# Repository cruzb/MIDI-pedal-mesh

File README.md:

# MIDI Pedal and Mesh
Digital music production today has a lot of limits. In an analog world a musician can slightly tweak the angle of their bow on a violin to get a different sound. The aim of the “Mesh” is to create a digital instrument with analog levels of control in package compatible with existing digital workflows.

Effects pedals are a common tool used by guitarists to modify the sound of their instrument. These devices are often designed to make one specific sound. The aim of the “Pedal” is to create a customizable audio processing device that gives users direct access to DSP hardware while maintaining the functionality and ease of use that musicians expect.

### Watch this video to see it in action

## Implementation
### Overview
The Mesh and Pedal work as standard audio components that can fit seamlessly into any musician’s kit. The Mesh outputs a MIDI signal which can be use to generate sound through any MIDI-capable synthesizer. The Pedal takes in analog audio and performs effects processing on it before outputting it to an amplifier or speaker for play. These devices can work in tandem, independently, or with other music devices.

### Pedal
- Users create effects programs on desktop and upload to the device EEPROM via a desktop application and USB connection
- Once loaded to the pedal programs can be selected via a knob
- An LCD screen in the pedal displays the active program and up to three associated parameters for it
- Input analog audio is split into two independent signal paths and processed by the selected program on an FV-1 DSP chip
- The affected signal then runs through an analog equalizer and is blended with the clean signal before it is output.

### Mesh
- Use strain sensors to read force data on two axes via ADC
- Use ADC data to do basic 2D localization of which point in grid is most pressed and by how much
- Map that point to a pitch, pitch-bend, and velocity for MIDI
- Generate MIDI packets from these data
- Send MIDI via UART at 31250 baud

## PCB Design
Three PCBs were created for this project. One for the pedal and two for the mesh. The pedal PCB contains over 160 components that handle digital and analog signals. The mesh PCBs are simpler but took special design considerations into account. Because of the analog nature of the device all analog runs were made as short as possible and processing occurs close to the sensors to deal with noise issues.

## Major Compontents
### Pedal
- PIC16F15355 Microcontroller
- FV-1 Spin Semiconductor DSP Chip
- HD44780-Compatible RGB 16x2 Character LCD
- FT232 USB-UART Interface
- 24LC32A External EEPROM Chip
- MAX4910ETE Audio Switch

### Mesh
- PIC16F15376 Microcontroller
- TAL221 Load Cell
- AD620 Differential Amplifier

#### Made with Jordan Frank, Ethan Brown, Charlie Light, and Spencer Haney for University of Michigan EECS 473

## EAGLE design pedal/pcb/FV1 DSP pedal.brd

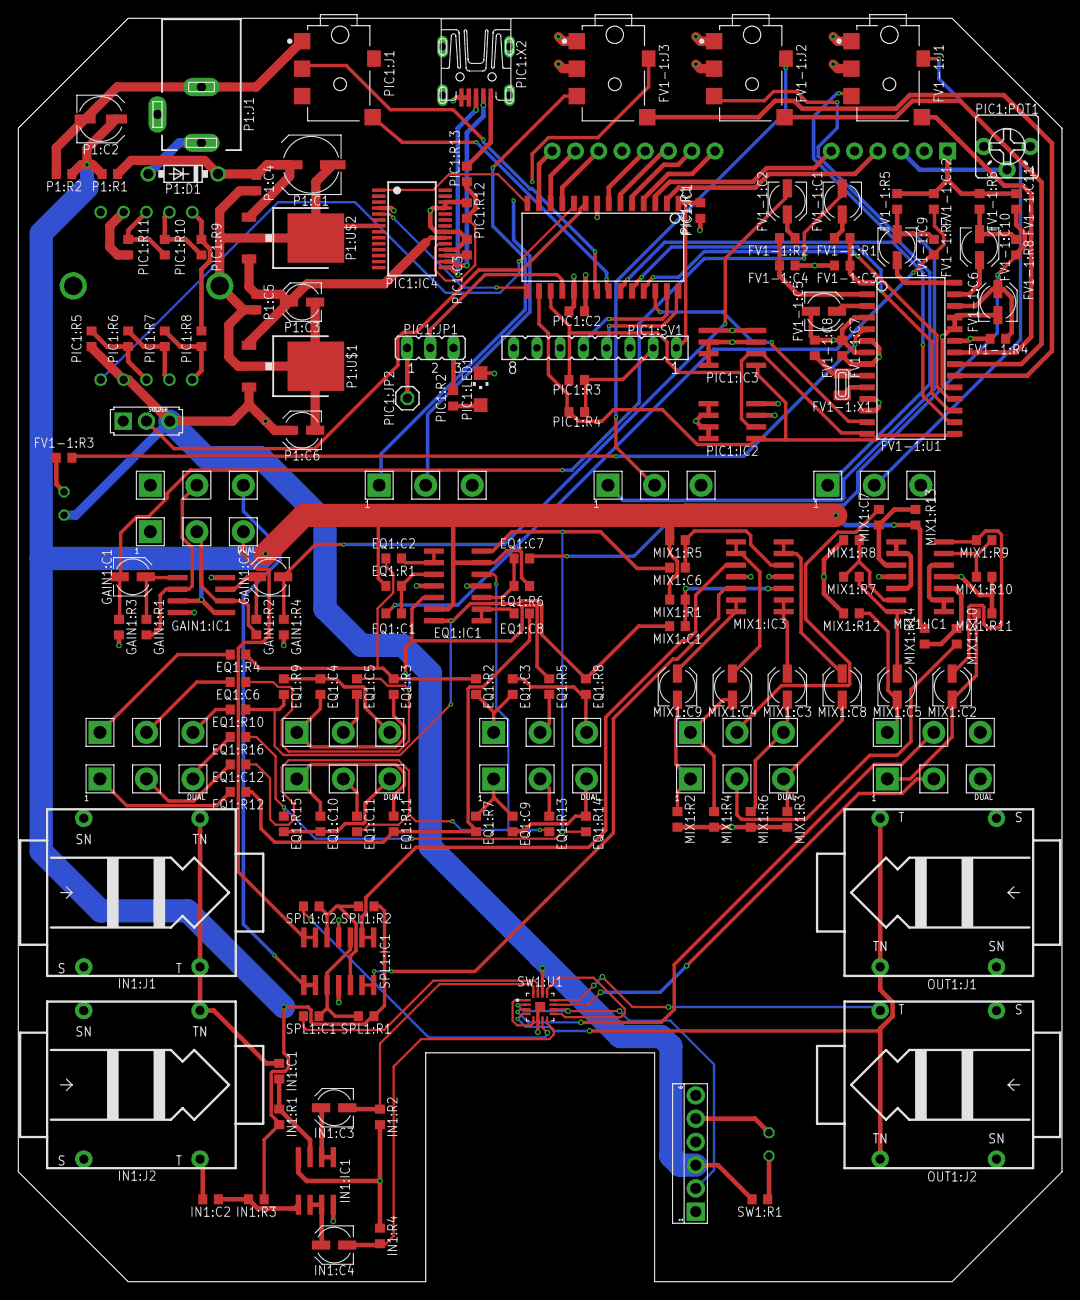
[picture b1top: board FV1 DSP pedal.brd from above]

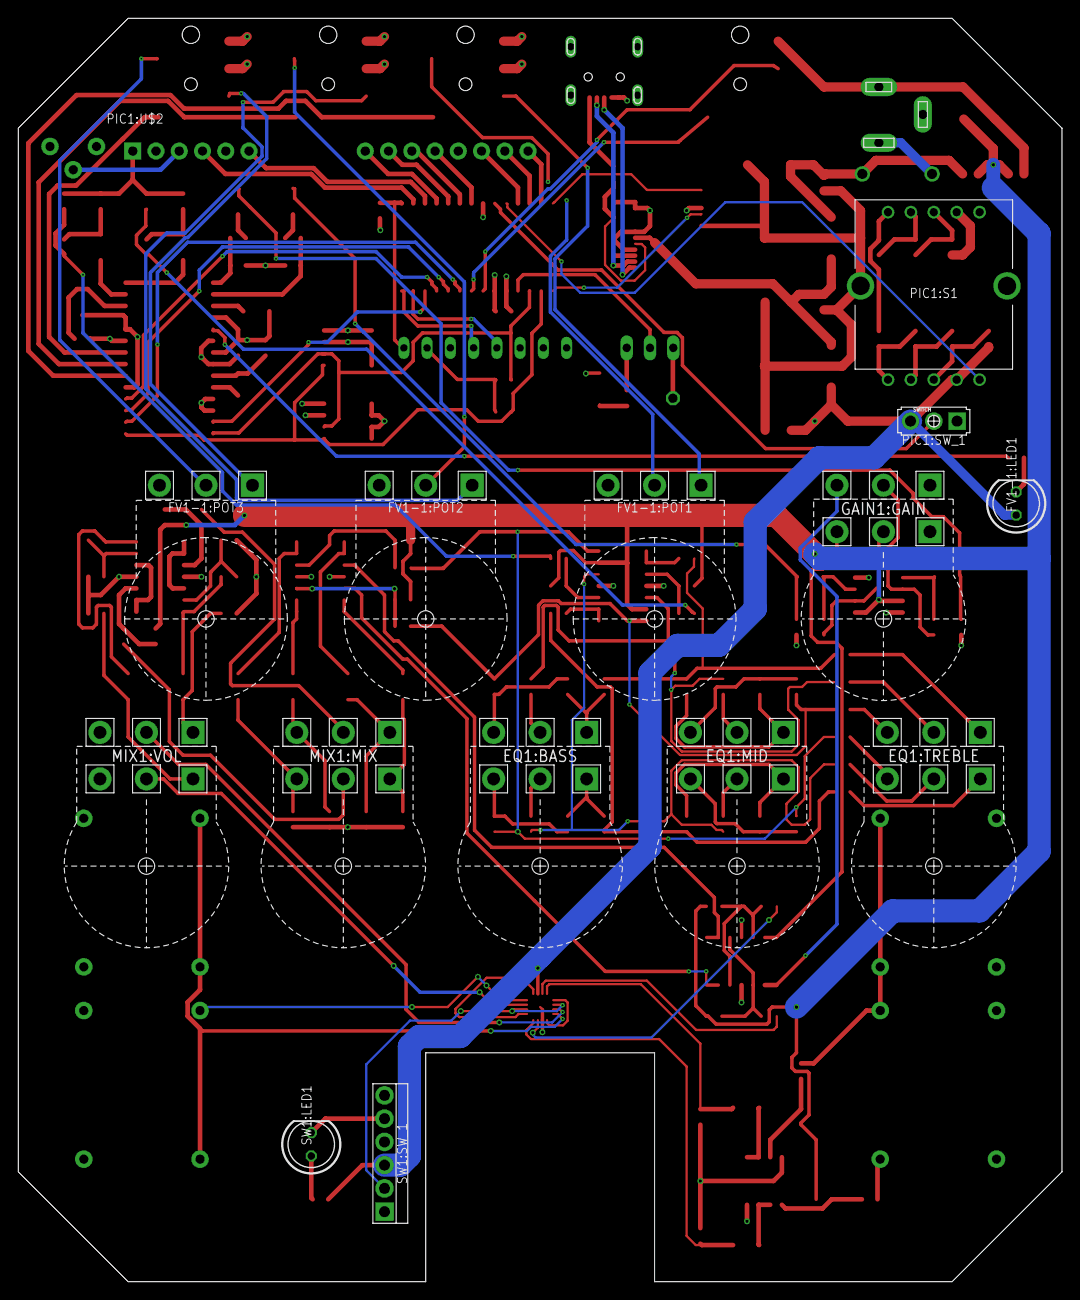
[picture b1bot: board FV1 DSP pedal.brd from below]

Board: 4 copper layers, 114.0 x 138.0 mm, 160 parts (4 on the bottom side), 152 nets.

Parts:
EQ1:BASS, EQ1:MID: B100k; 16MM_DUALGANG
EQ1:C1, EQ1:C7: 220n; RESISTOR_R0603
EQ1:C2, EQ1:C8: 1u; RESISTOR_R0603
EQ1:C3, EQ1:C9: 50n; RESISTOR_R0603
EQ1:C4, EQ1:C6, EQ1:C10, EQ1:C12: 5n; RESISTOR_R0603
EQ1:C5, EQ1:C11: 22n; RESISTOR_R0603
EQ1:IC1: TL074D; SO14
EQ1:R1, EQ1:R6: 1M; RESISTOR_R0603
EQ1:R2, EQ1:R5, EQ1:R7, EQ1:R8, EQ1:R13, EQ1:R14: 11k; RESISTOR_R0603
EQ1:R3, EQ1:R9, EQ1:R11, EQ1:R15: 3.6k; RESISTOR_R0603
EQ1:R4, EQ1:R10, EQ1:R12, EQ1:R16: 1.8k; RESISTOR_R0603
EQ1:TREBLE: B500k; 16MM_DUALGANG
FV1-1:C1, FV1-1:C2, FV1-1:C5, FV1-1:C6: 1u; UD-4X5,8_NICHICON
FV1-1:C3, FV1-1:C4: 1n; RESISTOR_R0603
FV1-1:C7: 100n; RESISTOR_R0603
FV1-1:C8: 15p; RESISTOR_R0603
FV1-1:C9, FV1-1:C10: 3.3u; UD-4X5,8_NICHICON
FV1-1:C11, FV1-1:C12: 2.2n; RESISTOR_R0603
FV1-1:J1, FV1-1:J2, FV1-1:J3: SJ2-25313D-SMT-TR; CUI_SJ2-25313D-SMT-TR
FV1-1:LED1: LED5MM
FV1-1:POT1, FV1-1:POT2, FV1-1:POT3: B10k; 16MM_B.MOUNT
FV1-1:R1, FV1-1:R2, FV1-1:R7, FV1-1:R8: 1k; RESISTOR_R0603
FV1-1:R3, FV1-1:R4: 100; RESISTOR_R0603
FV1-1:R5, FV1-1:R6: 10k; RESISTOR_R0603
FV1-1:U1: SO28W
FV1-1:X1: FC-135; XTAL3215
GAIN1:C1, GAIN1:C2: 10u; UD-4X5,8_NICHICON
GAIN1:GAIN: A50k; 16MM_DUALGANG
GAIN1:IC1: TL072D; SO08
GAIN1:R1: 33.3k; RESISTOR_R0603
GAIN1:R2: 33.3K; RESISTOR_R0603
GAIN1:R3, GAIN1:R4: 1M; RESISTOR_R0603
IN1:C1, IN1:C2: 220n; RESISTOR_R0603
IN1:C3, IN1:C4: 10u; UD-4X5,8_NICHICON
IN1:IC1: TL072D; SO08
IN1:J1, IN1:J2: SWITCHED_MONO_JACK; TS_SW
IN1:R1, IN1:R2, IN1:R3, IN1:R4: 1M; RESISTOR_R0603
MIX1:C1, MIX1:C6, MIX1:C7, MIX1:C10: 220n; RESISTOR_R0603
MIX1:C2, MIX1:C3, MIX1:C4, MIX1:C5, MIX1:C8, MIX1:C9: 10u; UD-4X5,8_NICHICON
MIX1:IC1, MIX1:IC3: TL074D; SO14
MIX1:MIX: B50k; 16MM_DUALGANG
MIX1:R1, MIX1:R2, MIX1:R3, MIX1:R4, MIX1:R5, MIX1:R6, MIX1:R11, MIX1:R12, MIX1:R13, MIX1:R14: 1M; RESISTOR_R0603
MIX1:R7, MIX1:R9: 200; RESISTOR_R0603
MIX1:R8, MIX1:R10: 100; RESISTOR_R0603
MIX1:VOL: A50k; 16MM_DUALGANG
OUT1:J1, OUT1:J2: SWITCHED_MONO_JACK; TS_SW
P1:C1: 47u; UD-6,3X5,8_NICHICON
P1:C2: 22u; UD-5X5,8_NICHICON
P1:C3, P1:C6: 2.2u; UD-4X5,8_NICHICON
P1:C4, P1:C5: 100n; RESISTOR_R0603
P1:D1: 1N5817-B; DO41-7.6
P1:J1: DCJ0202
P1:R1, P1:R2: 33k; RESISTOR_R0603
P1:U$1: LF33ABDT-TR; TO252
P1:U$2: LF50ABDT-TR; TO252
PIC1:C2, PIC1:C3: 100n; RESISTOR_R0603
PIC1:IC1: PIC16LF1516/18SO; SO28W
PIC1:IC2, PIC1:IC3: 24LC32ASN; SO-08
PIC1:IC4: FT232RL; SSOP28
PIC1:J1: SJ2-25313D-SMT-TR; CUI_SJ2-25313D-SMT-TR
PIC1:JP1: JP2
PIC1:JP2: 1X01
PIC1:LED1: CHIPLED_1206
PIC1:POT1: TRIM1
PIC1:R1: 50k; RESISTOR_R0603
PIC1:R2: 100; RESISTOR_R0603
PIC1:R3, PIC1:R4, PIC1:R5, PIC1:R6, PIC1:R7, PIC1:R8, PIC1:R9, PIC1:R10, PIC1:R11, PIC1:R12: 10k; RESISTOR_R0603
PIC1:R13: 4k7; RESISTOR_R0603
PIC1:S1: SR1712F-0108-20F0A-N9-N-027; SR1712F010820F0AN9N027
PIC1:SV1: FE08
PIC1:SW_1: SPDT.MINI
PIC1:U$2: LCD16X2RGB
PIC1:X2: MINI-USB-UX60-MB-5S8; UX60-MB-5S8
SPL1:C1, SPL1:C2: 220n; RESISTOR_R0603
SPL1:IC1: TL074D; SO14
SPL1:R1, SPL1:R2: 1M; RESISTOR_R0603
SW1:LED1: LED5MM
SW1:R1: 100; RESISTOR_R0603
SW1:SW_1: DPDT.WIRE
SW1:U1: MAX4910ETET; QFN50P300X300X80-17N

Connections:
3.3V: FV1-1:C7.2, FV1-1:J1.3, FV1-1:J2.3, FV1-1:J3.3, FV1-1:LED1.A, FV1-1:R4.2, FV1-1:U1.6, FV1-1:U1.8, FV1-1:U1.23, P1:C6.+, P1:U$1.2, PIC1:C2.1, PIC1:IC1.20, PIC1:IC2.8, PIC1:IC3.1, PIC1:IC3.8, PIC1:IC4.4, PIC1:POT1.3, PIC1:R1.1, PIC1:R3.2, PIC1:R4.1, PIC1:R5.1, PIC1:S1.2, PIC1:SV1.2, PIC1:SW_1.3, PIC1:U$2.2, PIC1:U$2.15, SW1:R1.1, SW1:SW_1.A3, SW1:U1.14
4.5V: EQ1:IC1.6, EQ1:IC1.13, EQ1:R1.1, EQ1:R6.1, GAIN1:IC1.3, GAIN1:IC1.5, IN1:R1.2, IN1:R3.2, MIX1:R1.2, MIX1:R5.1, MIX1:R13.2, MIX1:R14.2, P1:C2.+, P1:R1.1, P1:R2.2, SPL1:R1.2, SPL1:R2.2
9V: EQ1:IC1.4, GAIN1:IC1.8, IN1:IC1.8, MIX1:IC1.4, MIX1:IC3.4, P1:C1.+, P1:C4.1, P1:D1.C, P1:R1.2, P1:U$2.1, SPL1:IC1.4
EQ1:N$1: EQ1:C7.1, EQ1:IC1.10, EQ1:R6.2
EQ1:N$2: EQ1:C2.2, EQ1:IC1.1, EQ1:IC1.2
EQ1:N$3: EQ1:C2.1, EQ1:R2.2, EQ1:R3.2, EQ1:R4.2
EQ1:N$4: EQ1:BASS.1, EQ1:C3.2, EQ1:R2.1
EQ1:N$5: EQ1:C4.2, EQ1:MID.1, EQ1:R3.1
EQ1:N$6: EQ1:R4.1, EQ1:TREBLE.1
EQ1:N$7: EQ1:C4.1, EQ1:MID.3, EQ1:R9.2
EQ1:N$8: EQ1:R10.2, EQ1:TREBLE.3
EQ1:N$9: EQ1:C1.1, EQ1:IC1.3, EQ1:R1.2
EQ1:N$10: EQ1:BASS.3, EQ1:C3.1, EQ1:R8.2
EQ1:N$11: EQ1:C5.1, EQ1:C6.1, EQ1:IC1.5, EQ1:R5.2
EQ1:N$12: EQ1:C5.2, EQ1:MID.2
EQ1:N$13: EQ1:C6.2, EQ1:TREBLE.2
EQ1:N$14: EQ1:BASS.2, EQ1:R5.1
EQ1:N$16: EQ1:C8.2, EQ1:IC1.8, EQ1:IC1.9
EQ1:N$17: EQ1:C8.1, EQ1:R7.2, EQ1:R11.2, EQ1:R12.2
EQ1:N$18: EQ1:BASS.4, EQ1:C9.2, EQ1:R7.1
EQ1:N$19: EQ1:C10.2, EQ1:MID.4, EQ1:R11.1
EQ1:N$20: EQ1:R12.1, EQ1:TREBLE.4
EQ1:N$21: EQ1:C10.1, EQ1:MID.6, EQ1:R15.2
EQ1:N$22: EQ1:R16.2, EQ1:TREBLE.6
EQ1:N$23: EQ1:BASS.6, EQ1:C9.1, EQ1:R14.2
EQ1:N$25: EQ1:C11.1, EQ1:C12.1, EQ1:IC1.12, EQ1:R13.2
EQ1:N$26: EQ1:C11.2, EQ1:MID.5
EQ1:N$27: EQ1:C12.2, EQ1:TREBLE.5
EQ1:N$28: EQ1:BASS.5, EQ1:R13.1
FV1-1:N$1: FV1-1:J1.11, FV1-1:POT3.1
FV1-1:N$2: FV1-1:J1.10, FV1-1:POT3.2
FV1-1:N$3: FV1-1:J1.2, FV1-1:U1.22
FV1-1:N$4: FV1-1:C6.+, FV1-1:R4.1, FV1-1:U1.26
FV1-1:N$5: FV1-1:LED1.K, FV1-1:R3.1
FV1-1:N$6: FV1-1:C1.+, FV1-1:R1.1
FV1-1:N$7: FV1-1:R3.2, FV1-1:U1.5
FV1-1:N$8: FV1-1:C9.+, FV1-1:U1.28
FV1-1:N$9: FV1-1:C2.+, FV1-1:R2.1
FV1-1:N$10: FV1-1:C3.2, FV1-1:R1.2, FV1-1:U1.1
FV1-1:N$11: FV1-1:C4.2, FV1-1:R2.2, FV1-1:U1.2
FV1-1:N$12: FV1-1:C5.+, FV1-1:U1.3
FV1-1:N$13: FV1-1:C8.2, FV1-1:U1.9, FV1-1:X1.P$2
FV1-1:N$14: FV1-1:J2.10, FV1-1:POT2.2
FV1-1:N$15: FV1-1:J2.2, FV1-1:U1.21
FV1-1:N$16: FV1-1:J2.11, FV1-1:POT2.1
FV1-1:N$17: FV1-1:J3.11, FV1-1:POT1.1
FV1-1:N$18: FV1-1:J3.10, FV1-1:POT1.2
FV1-1:N$19: FV1-1:J3.2, FV1-1:U1.20
FV1-1:N$20: FV1-1:C10.+, FV1-1:U1.27
FV1-1:N$21: FV1-1:U1.10, FV1-1:X1.P$1
FV1-1:N$22: FV1-1:C9.-, FV1-1:R5.2, FV1-1:R7.1
FV1-1:N$23: FV1-1:C10.-, FV1-1:R6.2, FV1-1:R8.1
GAIN1:N$1: GAIN1:C1.+, GAIN1:IC1.1, GAIN1:R1.2
GAIN1:N$2: GAIN1:C2.+, GAIN1:IC1.7, GAIN1:R2.2
GAIN1:N$3: GAIN1:GAIN.5, GAIN1:IC1.6, GAIN1:R2.1
GAIN1:N$4: GAIN1:GAIN.2, GAIN1:IC1.2, GAIN1:R1.1
GND: EQ1:IC1.11, FV1-1:C3.1, FV1-1:C4.1, FV1-1:C5.-, FV1-1:C6.-, FV1-1:C7.1, FV1-1:C8.1, FV1-1:C11.1, FV1-1:C12.1, FV1-1:J1.1, FV1-1:J2.1, FV1-1:J3.1, FV1-1:POT1.3, FV1-1:POT2.3, FV1-1:POT3.3, FV1-1:R5.1, FV1-1:R6.1, FV1-1:U1.4, FV1-1:U1.7, FV1-1:U1.11, FV1-1:U1.12, FV1-1:U1.19, FV1-1:U1.24, FV1-1:U1.25, GAIN1:IC1.4, GAIN1:R3.1, GAIN1:R4.1, IN1:IC1.4, IN1:J1.S, IN1:J1.SN, IN1:J2.S, IN1:J2.SN, IN1:R2.1, IN1:R4.1, MIX1:IC1.11, MIX1:IC3.11, MIX1:R2.2, MIX1:R3.2, MIX1:R4.2, MIX1:R6.2, MIX1:R8.2, MIX1:R10.2, MIX1:R11.2, MIX1:R12.2, MIX1:VOL.3, MIX1:VOL.6, OUT1:J1.S, OUT1:J1.SN, OUT1:J2.S, OUT1:J2.SN, P1:C1.-, P1:C2.-, P1:C3.-, P1:C4.2, P1:C5.2, P1:C6.-, P1:J1.3, P1:R2.1, P1:U$1.3, P1:U$2.3, PIC1:C2.2, PIC1:C3.2, PIC1:IC1.8, PIC1:IC1.19, PIC1:IC2.1, PIC1:IC2.2, PIC1:IC2.3, PIC1:IC2.4, PIC1:IC2.7, PIC1:IC3.2, PIC1:IC3.3, PIC1:IC3.4, PIC1:IC3.7, PIC1:IC4.7, PIC1:IC4.18, PIC1:IC4.21, PIC1:IC4.25, PIC1:IC4.26, PIC1:J1.1, PIC1:LED1.C, PIC1:POT1.1, PIC1:R11.2, PIC1:R12.2, PIC1:S1.9, PIC1:S1.MH1, PIC1:S1.MH2, PIC1:SV1.3, PIC1:SW_1.1, PIC1:U$2.1, PIC1:U$2.5, PIC1:X2.4, PIC1:X2.5, SPL1:IC1.11, SW1:SW_1.A1, SW1:SW_1.B3, SW1:U1.6, SW1:U1.17
IN1:N$1: IN1:C1.2, IN1:J1.T, IN1:J1.TN, IN1:J2.TN
IN1:N$3: IN1:C3.+, IN1:IC1.1, IN1:IC1.2
IN1:N$5: IN1:C2.1, IN1:IC1.5, IN1:R3.1
IN1:N$6: IN1:C1.1, IN1:IC1.3, IN1:R1.1
IN1:N$7: IN1:C4.+, IN1:IC1.6, IN1:IC1.7
IN1:N$8: IN1:C2.2, IN1:J2.T
MIX1:N$1: MIX1:C4.-, MIX1:MIX.1, MIX1:R4.1
MIX1:N$2: MIX1:IC1.8, MIX1:IC1.9, MIX1:IC1.12
MIX1:N$3: MIX1:IC1.13, MIX1:R9.1, MIX1:R10.1
MIX1:N$4: MIX1:C2.+, MIX1:IC1.14, MIX1:R9.2
MIX1:N$5: MIX1:C3.-, MIX1:MIX.3, MIX1:R6.1
MIX1:N$6: MIX1:C7.1, MIX1:IC1.3, MIX1:R13.1
MIX1:N$7: MIX1:C4.+, MIX1:IC3.1, MIX1:IC3.2
MIX1:N$8: MIX1:C3.+, MIX1:IC3.8, MIX1:IC3.9
MIX1:N$9: MIX1:C10.1, MIX1:IC1.10, MIX1:R14.1
MIX1:N$10: MIX1:C10.2, MIX1:MIX.5
MIX1:N$11: MIX1:C7.2, MIX1:MIX.2
MIX1:N$13: MIX1:C9.-, MIX1:MIX.4, MIX1:R2.1
MIX1:N$14: MIX1:C6.1, MIX1:IC3.12, MIX1:R5.2
MIX1:N$15: MIX1:C1.1, MIX1:IC3.10, MIX1:R1.1
MIX1:N$18: MIX1:C9.+, MIX1:IC3.6, MIX1:IC3.7
MIX1:N$19: MIX1:IC1.1, MIX1:IC1.2, MIX1:IC1.5
MIX1:N$20: MIX1:C8.-, MIX1:MIX.6, MIX1:R3.1
MIX1:N$21: MIX1:C8.+, MIX1:IC3.13, MIX1:IC3.14
MIX1:N$22: MIX1:IC1.6, MIX1:R7.1, MIX1:R8.1
MIX1:N$23: MIX1:C5.+, MIX1:IC1.7, MIX1:R7.2
MIX1:N$25: MIX1:C2.-, MIX1:R11.1, MIX1:VOL.4
MIX1:N$28: MIX1:C5.-, MIX1:R12.1, MIX1:VOL.1
unnamed: MIX1:IC3.3, SPL1:IC1.8, SPL1:IC1.9
unnamed: MIX1:IC3.5, SPL1:IC1.6, SPL1:IC1.7
unnamed: EQ1:IC1.7, EQ1:R8.1, EQ1:R9.1, EQ1:R10.1, MIX1:C1.2
unnamed: EQ1:IC1.14, EQ1:R14.1, EQ1:R15.1, EQ1:R16.1, MIX1:C6.2
unnamed: GAIN1:GAIN.6, SPL1:IC1.13, SPL1:IC1.14
unnamed: GAIN1:GAIN.3, SPL1:IC1.1, SPL1:IC1.2
unnamed: IN1:C3.-, IN1:R2.2, SW1:U1.16
unnamed: FV1-1:C1.-, GAIN1:C1.-, GAIN1:R3.2
unnamed: FV1-1:C2.-, GAIN1:C2.-, GAIN1:R4.2
unnamed: EQ1:C1.2, FV1-1:C12.2, FV1-1:R7.2
unnamed: EQ1:C7.2, FV1-1:C11.2, FV1-1:R8.2
unnamed: IN1:C4.-, IN1:R4.2, SW1:U1.8
unnamed: OUT1:J1.T, OUT1:J1.TN, OUT1:J2.TN, SW1:U1.4
unnamed: OUT1:J2.T, SW1:U1.12
unnamed: P1:C3.+, P1:C5.1, P1:U$1.1, P1:U$2.2, PIC1:IC4.20
unnamed: SPL1:C1.2, SW1:U1.15
unnamed: SPL1:C2.2, SW1:U1.7
unnamed: MIX1:VOL.5, SW1:U1.11
unnamed: MIX1:VOL.2, SW1:U1.3
unnamed: FV1-1:U1.13, PIC1:IC1.26
unnamed: FV1-1:U1.18, PIC1:IC1.25
unnamed: FV1-1:U1.17, PIC1:IC1.24
unnamed: FV1-1:U1.16, PIC1:IC1.23
unnamed: FV1-1:U1.14, PIC1:IC1.17, PIC1:IC2.6, PIC1:IC3.6, PIC1:R3.1
unnamed: FV1-1:U1.15, PIC1:IC1.16, PIC1:IC2.5, PIC1:IC3.5, PIC1:R4.2
P1:N$27: P1:D1.A, P1:J1.1
PIC1:!MCLR: PIC1:IC1.1, PIC1:R1.2, PIC1:SV1.1
PIC1:ICSPCLK: PIC1:IC1.27, PIC1:SV1.5
PIC1:ICSPDAT: PIC1:IC1.28, PIC1:SV1.4
PIC1:INT_EXT: PIC1:IC1.9, PIC1:SW_1.2
PIC1:LCD_D4: PIC1:IC1.4, PIC1:U$2.11
PIC1:LCD_D5: PIC1:IC1.5, PIC1:U$2.12
PIC1:LCD_D6: PIC1:IC1.6, PIC1:U$2.13
PIC1:LCD_D7: PIC1:IC1.7, PIC1:U$2.14
PIC1:LCD_EN: PIC1:IC1.3, PIC1:U$2.6
PIC1:LCD_RS: PIC1:IC1.2, PIC1:U$2.4
PIC1:MIDI_RX: PIC1:IC1.22, PIC1:J1.2
PIC1:MIDI_TX: PIC1:IC1.21, PIC1:J1.3
PIC1:N$1: PIC1:IC1.18, PIC1:JP1.2
PIC1:N$2: PIC1:JP1.1, PIC1:JP2.1
PIC1:N$3: PIC1:C3.1, PIC1:IC4.17
PIC1:N$4: PIC1:IC4.19, PIC1:R12.1, PIC1:R13.2
PIC1:N$5: PIC1:JP1.3, PIC1:R2.2
PIC1:N$6: PIC1:LED1.A, PIC1:R2.1
PIC1:N$7: PIC1:R13.1, PIC1:X2.1
PIC1:N$9: PIC1:R5.2, PIC1:R6.1, PIC1:S1.3
PIC1:N$10: PIC1:R6.2, PIC1:R7.1, PIC1:S1.4
PIC1:N$11: PIC1:R7.2, PIC1:R8.1, PIC1:S1.5
PIC1:N$12: PIC1:R8.2, PIC1:R9.1, PIC1:S1.6
PIC1:N$13: PIC1:R9.2, PIC1:R10.1, PIC1:S1.7
PIC1:N$14: PIC1:R10.2, PIC1:R11.1, PIC1:S1.8
PIC1:N$16: PIC1:POT1.2, PIC1:U$2.3
PIC1:PWM3: PIC1:IC1.11, PIC1:U$2.16
PIC1:PWM4: PIC1:IC1.12, PIC1:U$2.17
PIC1:PWM5: PIC1:IC1.13, PIC1:U$2.18
PIC1:P_SEL: PIC1:IC1.10, PIC1:S1.1
PIC1:USB_DM: PIC1:IC4.16, PIC1:X2.2
PIC1:USB_DP: PIC1:IC4.15, PIC1:X2.3
PIC1:USB_RX: PIC1:IC1.14, PIC1:IC4.1
PIC1:USB_TX: PIC1:IC1.15, PIC1:IC4.5
SPL1:N$3: SPL1:C2.1, SPL1:IC1.5, SPL1:IC1.12, SPL1:R2.1
SPL1:N$5: SPL1:C1.1, SPL1:IC1.3, SPL1:IC1.10, SPL1:R1.1
SW1:CB: SW1:SW_1.A2, SW1:U1.2, SW1:U1.10
SW1:N$1: SW1:LED1.K, SW1:SW_1.B2
SW1:N$5: SW1:LED1.A, SW1:R1.2
SW1:NC_12: SW1:U1.1, SW1:U1.5
SW1:NC_34: SW1:U1.9, SW1:U1.13

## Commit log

2019-12-07 upload final project

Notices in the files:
parts and their libraries:
SparkFun-Displays-modified: Licensing: Creative Commons ShareAlike 4.0 International - https://creativecommons.org/licenses/by-sa/4.0
